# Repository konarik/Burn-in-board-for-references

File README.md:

# Burn-in-board-for-references

The PCB is used to burn in voltage references like REF0x, LT1021, LT1019 ...

Resistors R1 ... R20 can be used as load for the reference. Resistor R21 sets the current for the ON status LED diode.

Voltages can be monitor via 25 pin DB-25 connector or each reference can have it's own 2 pin 2.54mm header.

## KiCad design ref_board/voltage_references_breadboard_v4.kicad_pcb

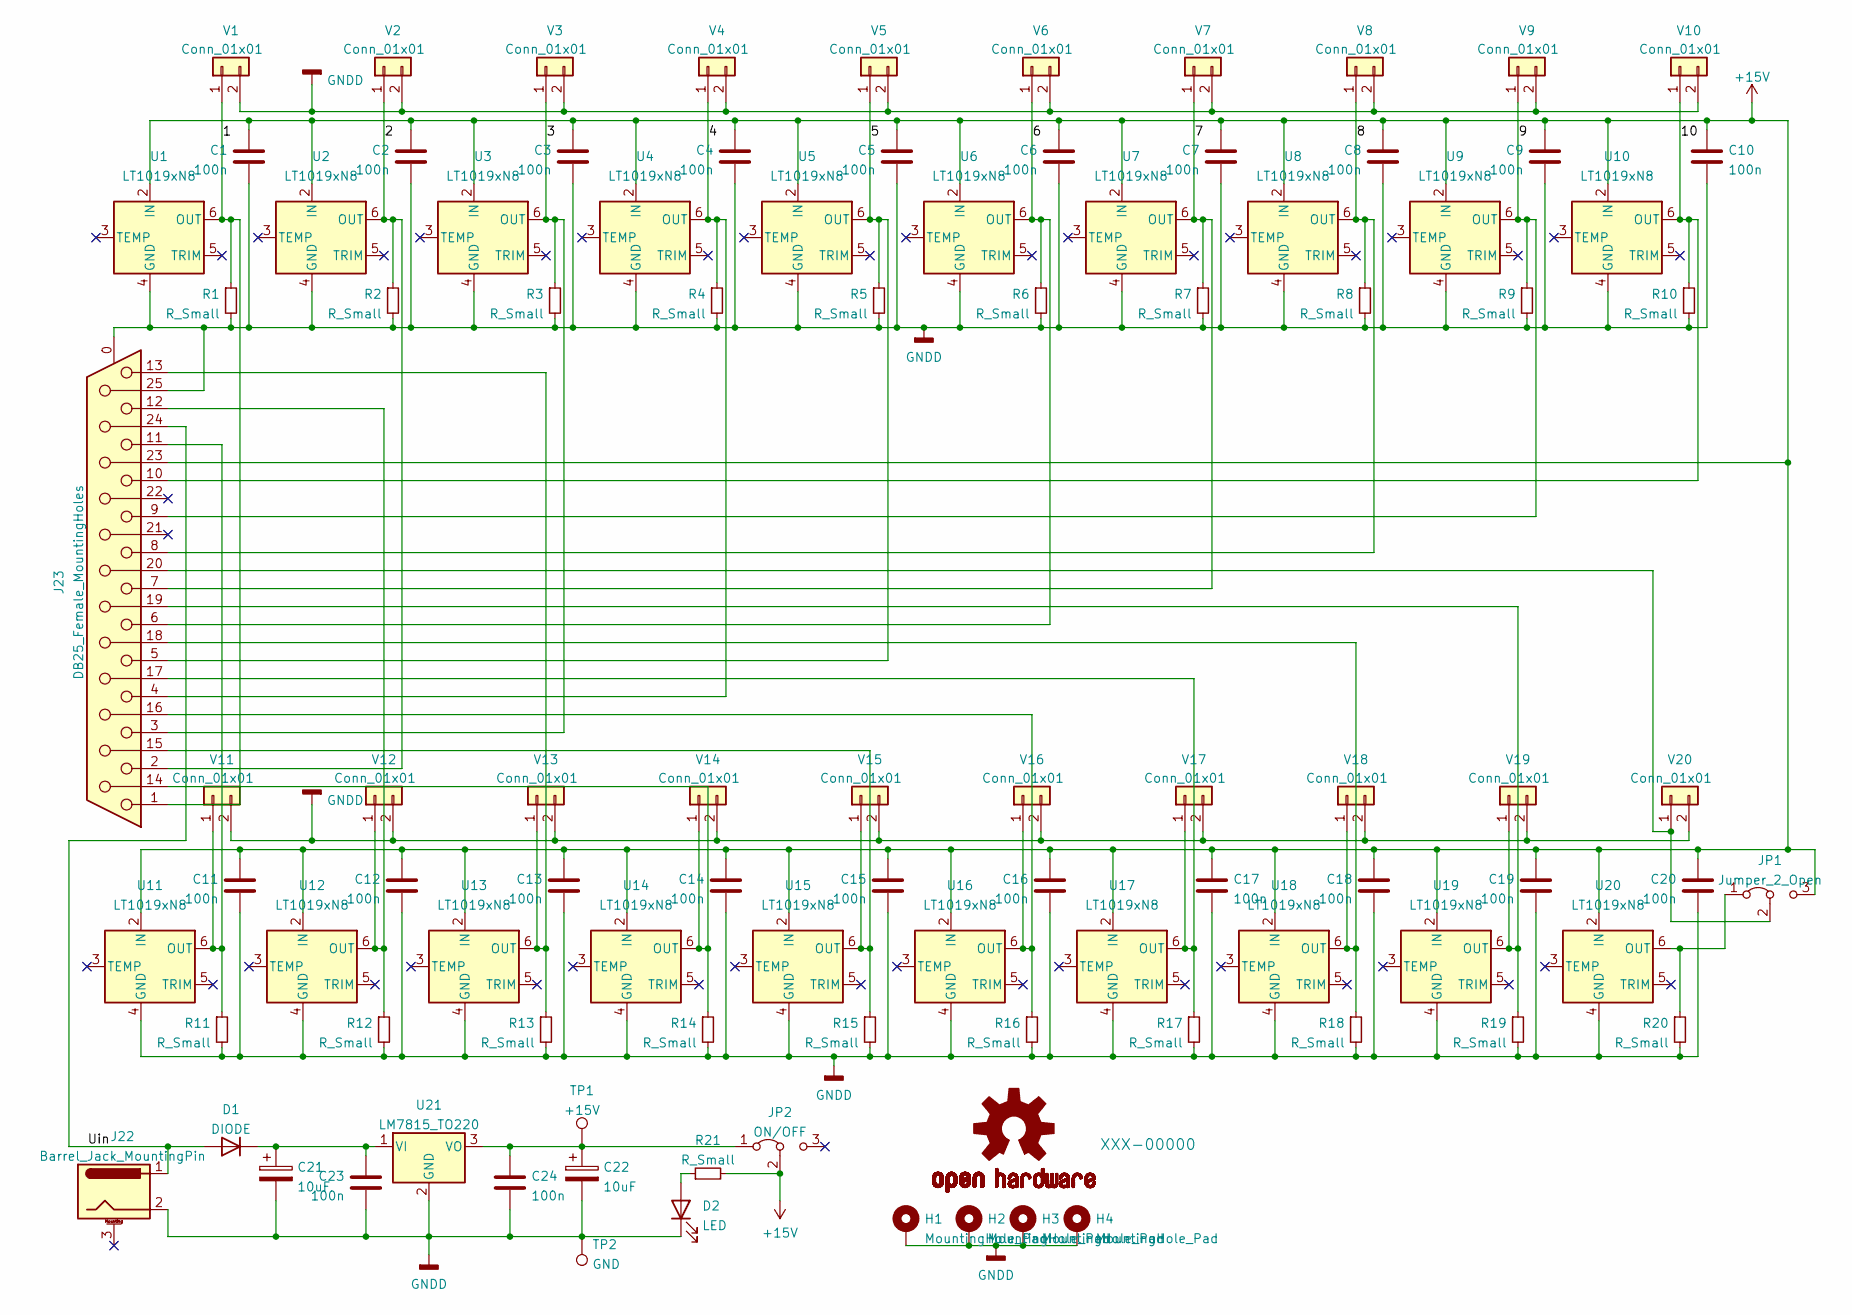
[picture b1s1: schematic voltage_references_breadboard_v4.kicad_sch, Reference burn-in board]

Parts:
C1, C2, C3, C4, C5, C6, C7, C8, C9, C10, C11, C12, C13, C14, C15, C16, C17, C18, C19, C20, C23, C24: 100n; C_Rect_L7.0mm_W3.5mm_P2.50mm_P5.00mm
C21, C22: 10uF; CP_Radial_D10.0mm_P2.50mm_P5.00mm
D1: DIODE; D_DO-41_SOD81_P10.16mm_Horizontal
D2: LED; LED_D5.0mm
H1, H2, H3, H4: MountingHole_Pad; MountingHole_3.2mm_M3_Pad_Via
J22: Barrel_Jack_MountingPin; BarrelJack_Horizontal
J23: DB25_Female_MountingHoles; DSUB-25_Female_Horizontal_P2.77x2.84mm_EdgePinOffset7.70mm_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
JP1: Jumper_2_Open; PinHeader_1x03_P2.54mm_Vertical
JP2: ON/OFF; PinHeader_1x03_P2.54mm_Vertical
LOGO1: OSHW-LOGOL; OSHW-Logo2_7.3x6mm_SilkScreen
R1, R2, R3, R4, R5, R6, R7, R8, R9, R10, R11, R12, R13, R14, R15, R16, R17, R18, R19, R20, R21: R_Small; THT_R_1206_3216Metric_Pad1.30x1.75mm_HandSolder
TP1: +15V; TestPoint_THTPad_D2.5mm_Drill1.2mm
TP2: GND; TestPoint_THTPad_D2.5mm_Drill1.2mm
U1, U2, U3, U4, U5, U6, U7, U8, U9, U10, U11, U12, U13, U14, U15, U16, U17, U18, U19, U20: LT1019xN8; DIP-8_W7.62mm_Socket
U21: LM7815_TO220; TO-220-3_Vertical
V1, V2, V3, V4, V5, V6, V7, V8, V9, V10, V11, V12, V13, V14, V15, V16, V17, V18, V19, V20: Conn_01x01; PinHeader_1x02_P2.54mm_Vertical

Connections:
+15V: C1.1, C2.1, C3.1, C4.1, C5.1, C6.1, C7.1, C8.1, C9.1, C10.1, C11.1, C12.1, C13.1, C14.1, C15.1, C16.1, C17.1, C18.1, C19.1, C20.1, J23.23, JP1.3 (B), JP2.2 (C), R21.2, U1.2 (IN), U2.2 (IN), U3.2 (IN), U4.2 (IN), U5.2 (IN), U6.2 (IN), U7.2 (IN), U8.2 (IN), U9.2 (IN), U10.2 (IN), U11.2 (IN), U12.2 (IN), U13.2 (IN), U14.2 (IN), U15.2 (IN), U16.2 (IN), U17.2 (IN), U18.2 (IN), U19.2 (IN), U20.2 (IN)
/1: J23.1, R1.1, U1.6 (OUT), V1.1
/2: J23.2, R2.1, U2.6 (OUT), V2.1
/3: J23.3, R3.1, U3.6 (OUT), V3.1
/4: J23.4, R4.1, U4.6 (OUT), V4.1
/5: J23.5, R5.1, U5.6 (OUT), V5.1
/6: J23.6, R6.1, U6.6 (OUT), V6.1
/7: J23.7, R7.1, U7.6 (OUT), V7.1
/8: J23.8, R8.1, U8.6 (OUT), V8.1
/9: J23.9, R9.1, U9.6 (OUT), V9.1
/10: J23.10, R10.1, U10.6 (OUT), V10.1
/Uin: D1.2 (A), J22.1, J23.24
GNDD: C1.2, C2.2, C3.2, C4.2, C5.2, C6.2, C7.2, C8.2, C9.2, C10.2, C11.2, C12.2, C13.2, C14.2, C15.2, C16.2, C17.2, C18.2, C19.2, C20.2, C21.2, C22.2, C23.2, C24.2, D2.1 (K), H1.1, H2.1, H3.1, H4.1, J22.2, J23.0 (PAD), J23.25, R1.2, R2.2, R3.2, R4.2, R5.2, R6.2, R7.2, R8.2, R9.2, R10.2, R11.2, R12.2, R13.2, R14.2, R15.2, R16.2, R17.2, R18.2, R19.2, R20.2, TP2.1, U1.4 (GND), U2.4 (GND), U3.4 (GND), U4.4 (GND), U5.4 (GND), U6.4 (GND), U7.4 (GND), U8.4 (GND), U9.4 (GND), U10.4 (GND), U11.4 (GND), U12.4 (GND), U13.4 (GND), U14.4 (GND), U15.4 (GND), U16.4 (GND), U17.4 (GND), U18.4 (GND), U19.4 (GND), U20.4 (GND), U21.2 (GND), V1.2, V2.2, V3.2, V4.2, V5.2, V6.2, V7.2, V8.2, V9.2, V10.2, V11.2, V12.2, V13.2, V14.2, V15.2, V16.2, V17.2, V18.2, V19.2, V20.2
unnamed: C21.1, C23.1, D1.1 (K), U21.1 (VI)
unnamed: C22.1, C24.1, JP2.1 (A), TP1.1, U21.3 (VO)
unnamed: D2.2 (A), R21.1
unnamed: J23.11, R11.1, U11.6 (OUT), V11.1
unnamed: J23.12, R12.1, U12.6 (OUT), V12.1
unnamed: J23.13, R13.1, U13.6 (OUT), V13.1
unnamed: J23.14, R14.1, U14.6 (OUT), V14.1
unnamed: J23.15, R15.1, U15.6 (OUT), V15.1
unnamed: J23.16, R16.1, U16.6 (OUT), V16.1
unnamed: J23.17, R17.1, U17.6 (OUT), V17.1
unnamed: J23.18, R18.1, U18.6 (OUT), V18.1
unnamed: J23.19, R19.1, U19.6 (OUT), V19.1
unnamed: J23.20, JP1.2 (C), V20.1
unnamed: JP1.1 (A), R20.1, U20.6 (OUT)

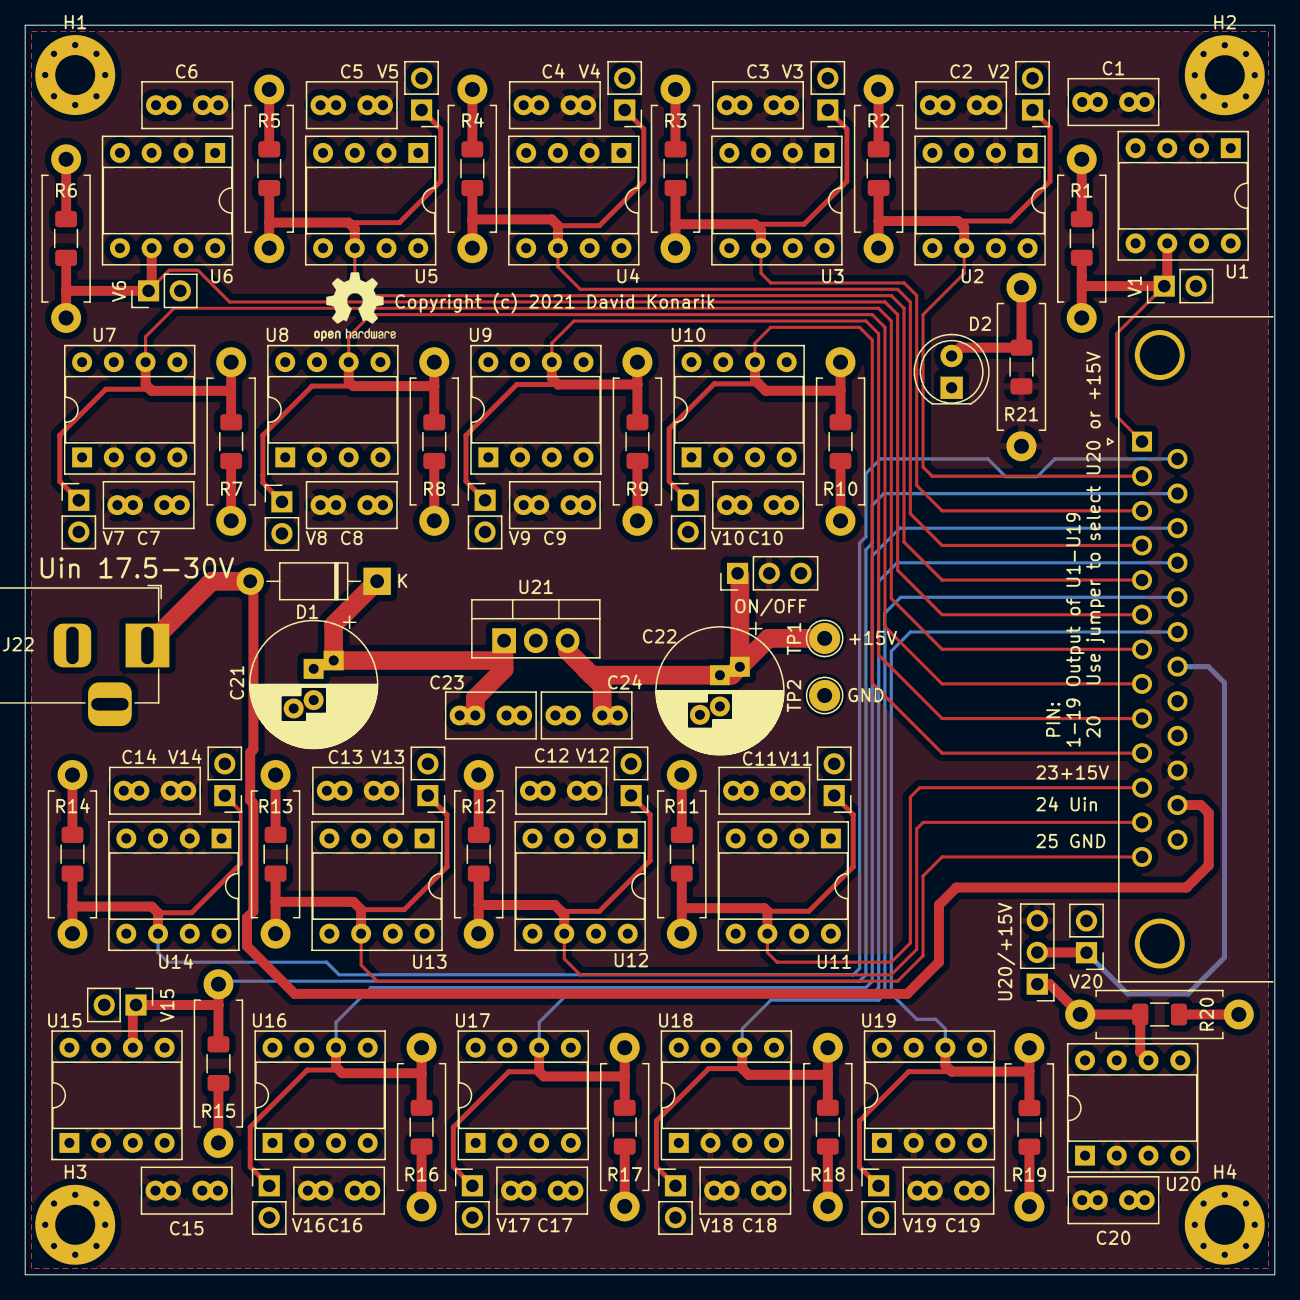
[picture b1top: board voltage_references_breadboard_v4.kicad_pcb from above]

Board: 2 copper layers, 100.0 x 100.0 mm, 99 parts (0 on the bottom side), 27 nets.

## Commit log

2022-04-17 LM399 cap directory created

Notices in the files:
ref_board/voltage_references_breadboard_v4.kicad_pcb:
Copyright (c) 2021 David Konarik
